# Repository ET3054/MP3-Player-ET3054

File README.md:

# MP3-Player-ET3054

Einrichtung:          		Hochschule für Wirtschaft und Recht Berlin

Jahrgang:                  	2024

Studierende:               	Bruno Storp
                           	Niclas Konzack
                           
Modul:                     	ET3054 Produktentwicklung

Zielsetzung des Projekts:  	Entwicklung eines MP3-Players, welcher auch leistungsstärkere Kopfhöher (Benchmark Sennheiser HD650) ohne qualitative Einschränkungen betreiben kann

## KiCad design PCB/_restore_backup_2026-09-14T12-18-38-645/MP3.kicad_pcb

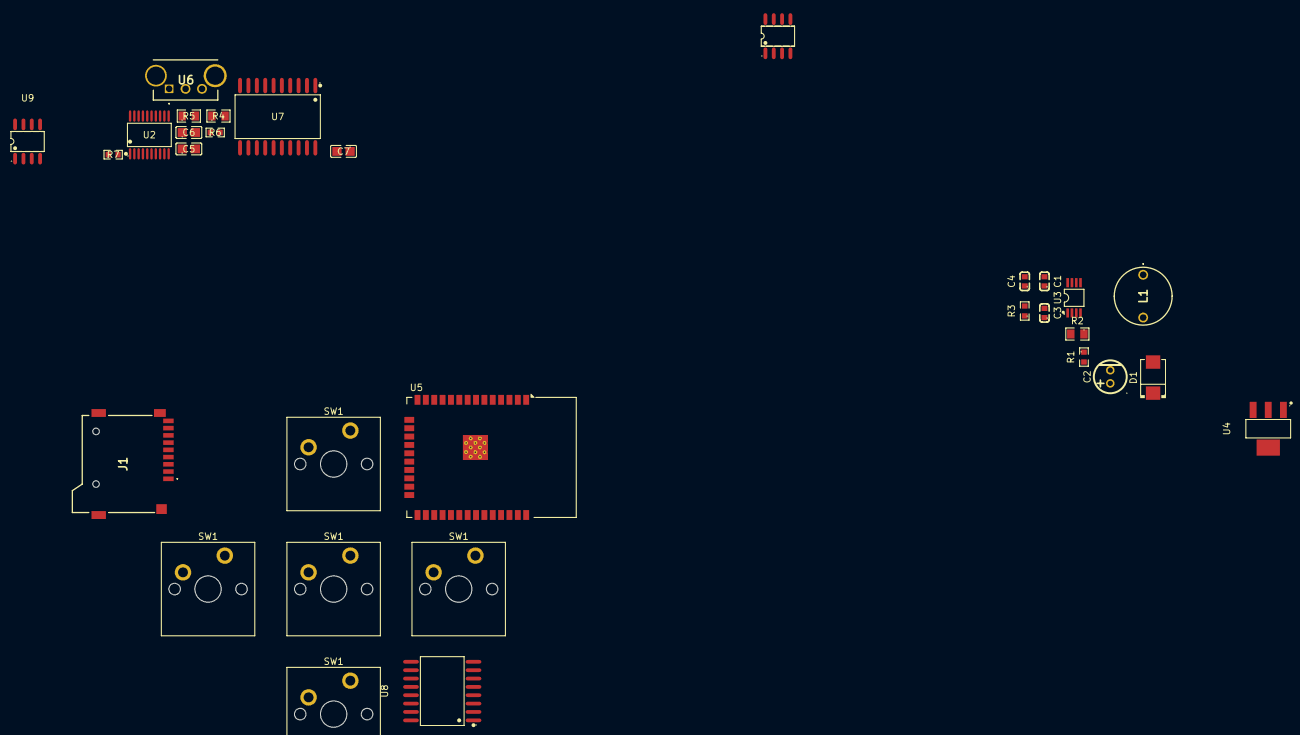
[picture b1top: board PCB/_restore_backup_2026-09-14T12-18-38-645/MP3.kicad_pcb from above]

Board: 2 copper layers, 31 parts (0 on the bottom side), 14 nets, no tracks yet.

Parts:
C1, C4: 33nF (333) ±10% 50V; C1614_C0603
C2: 47uF 35V; C40063_CAP-TH_BD5_0-P2_00-D0_8-FD
C3: 10pF (100) ±5% 50V; C1634_C0603
C5, C7: CL21A226MAYNNNE; C602037_C0805
C6: 47uF (476) ±20% 6.3V; C16780_C0805
D1: MBRS130LT3G; C51771_SMB_L4_6-W3_6-LS5_3-RD
J1: MSD-4-A; MSD4A
L1: 744750230150
R1: 147KΩ (1473) ±1%; C22878_R0603
R2, R4, R5: 10KΩ (1002) ±1%; C17414_R0805
R3: 20KΩ (2002) ±1%; C4184_R0603
R6, R7: 100KΩ (1003) ±1%; C25803_R0603
SW1, SW1#2, SW1#3, SW1#4, SW1#5: SW_Push; SW_Cherry_MX_PCB_1.00u
U1: AD8397ARZ-REEL7; C521305_SOIC-8_L4_9-W3_9-P1_27-LS6_0-BL
U2: PCM5102APWR; C107671_TSSOP-20_L6_5-W4_4-P0_65-LS6_4-BL
U3: ADP1613ARMZ-R7; C132279_MSOP-8_L3_0-W3_0-P0_65-LS4_9-BL
U4: LT3080EST#TRPBF; C107704_SOT-223_L6_5-W3_5-P2_30-LS7_0-BR_ST_VNL5050N3TR-E
U5: ESP32-WROOM-32D
U6: EC10E1260502
U7: LM1972MX/NOPB; C2649339_SOIC-20_L13_0-W7_6-P1_27-LS10_3-BL
U8: MC14490DWR2G; C223556_SOIC-16_L10_3-W7_5-P1_27-LS10_3-BL
U9: TLE2426ID; C353015_SOIC-8_L4_9-W3_9-P1_27-LS6_0-BL

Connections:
0: C1.2, C2.2, C3.2, C4.2, C6.1, R2.1, R5.1, U3.4 (GND)
+3.3V: L1.1, U3.3 (EN), U3.6 (VIN), U3.7 (FREQ)
+9V: R4.2, U7.3 (GND1), U7.19 (GND2)
unnamed: C4.1, R3.2
unnamed: C6.2, R4.1, R5.2, R6.1, R7.1 (1_1)
unnamed: D1.2 (A), L1.2, U3.5 (SW)
unnamed: C2.1, D1.1 (C), R1.2
unnamed: C5.1, U2.6 (OUTL_6)
unnamed: C3.1, R3.1, U3.1 (COMP)
unnamed: R1.1, R2.2, U3.2 (FB)
unnamed: C1.1, U3.8 (SS)
unnamed: U5.1 (GND), U5.15 (GND), U5.38 (GND), U5.39 (GND)
unnamed: C5.2, R6.2, U7.20 (IN2)
unnamed: C7.1 (1_1), U7.17 (OUT2)

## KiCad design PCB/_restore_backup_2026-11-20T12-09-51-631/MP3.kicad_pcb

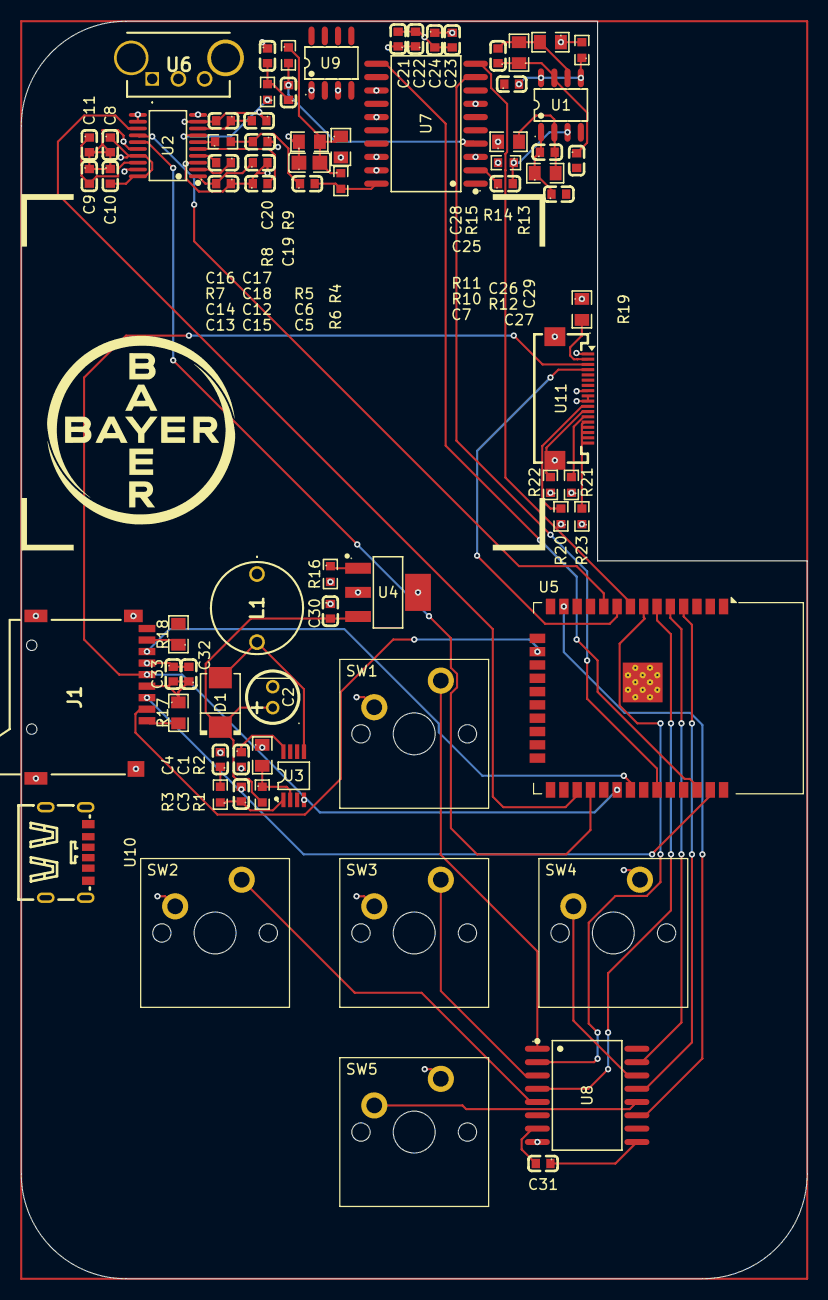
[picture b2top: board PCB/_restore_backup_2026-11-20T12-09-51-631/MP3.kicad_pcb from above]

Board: 4 copper layers, 75.0 x 120.0 mm, 75 parts (0 on the bottom side), 64 nets.

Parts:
C1, C4: 33nF (333) ±10% 50V; C1614_C0603
C2: 47uF 35V; C40063_CAP-TH_BD5_0-P2_00-D0_8-FD
C3: 10pF (100) ±5% 50V; C1634_C0603
C5, C19: 4.7uF (475) ±10% 10V; C1705_C0603
C6: 47uF (476) ±20% 6.3V; C16780_C0805
C7, C14, C15, C25, C27, C29: 2.2uF (225) ±10% 16V; C23630_C0603
C8, C9, C12, C16, C18, C20, C21, C24, C32: 100nF (104) ±10% 25V; C1590_C0603
C10, C11, C13, C17, C22, C23, C33: 贴片电容/10uF (106) ±20% 25V; C76614_C0603
C26, C28: 120pF; C107035_C0603
C30, C31: 1uF (105) ±10% 25V X7R; C29936_C0603
D1: MBRS130LT3G; C51771_SMB_L4_6-W3_6-LS5_3-RD
J1: MSD-4-A; MSD4A
L1: 744750230150
R1: 147KΩ (1473) ±1%; C22878_R0603
R2, R4, R5, R11, R12, R14, R15, R17, R18, R19: 10KΩ (1002) ±1%; C17414_R0805
R3: 20KΩ (2002) ±1%; C4184_R0603
R6, R9, R10, R13: 100KΩ (1003) ±1%; C25803_R0603
R7, R8: 470Ω (471) ±5%; C25241_R0603
R16: RC0603FR-071M8L; C137772_R0603
R20, R21, R22, R23: 27Ω (27R0) ±1%; C25190_R0603
SW1, SW2, SW3, SW4, SW5: SW_Push; SW_Cherry_MX_PCB_1.00u
U1: AD8397ARZ-REEL7; C521305_SOIC-8_L4_9-W3_9-P1_27-LS6_0-BL
U2: PCM5102APWR; C107671_TSSOP-20_L6_5-W4_4-P0_65-LS6_4-BL
U3: ADP1613ARMZ-R7; C132279_MSOP-8_L3_0-W3_0-P0_65-LS4_9-BL
U4: LT3080EST#TRPBF; C107704_SOT-223_L6_5-W3_5-P2_30-LS7_0-BR_ST_VNL5050N3TR-E
U5: ESP32-WROOM-32D
U6: EC10E1260502
U7: LM1972MX/NOPB; C2649339_SOIC-20_L13_0-W7_6-P1_27-LS10_3-BL
U8: MC14490DWR2G; C223556_SOIC-16_L10_3-W7_5-P1_27-LS10_3-BL
U9: TLE2426ID; C353015_SOIC-8_L4_9-W3_9-P1_27-LS6_0-BL
U10: USB-TYPE-C-009; C2927029_TYPE-C-SMD_TYPE-C-6P
U11: FPC 0.5-18P HYH2.0; C6364663_FPC-SMD_18P-P0_50_FPC-0_5-18P-HYH2_0

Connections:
0: C1.2, C2.2, C3.2, C4.2, C8.2, C9.1, C10.1, C11.2, C30.1, C32.1, C33.2, J1.6 (VSS), J1.G1 (GND_1), J1.G2 (GND_2), J1.G3 (GND_3), J1.G4 (GND_4), R2.1, R16.2, R20.1, R21.1, R22.1, R23.1, SW1.1, SW2.1, SW3.1, SW4.2, SW5.2, U1.4 (-VS), U2.10 (DEMP), U2.11 (FLT), U2.12 (SCK), U2.16 (FMT), U2.19 (DGND), U3.4 (GND), U7.1 (GND_AC), U7.5 (GND_AC), U7.6 (GND_AC), U7.8 (LOGIC_GND), U7.14 (GND_AC), U7.16 (GND_AC), U8.8 (VSS), U9.2 (COMMON), U11.1, U11.8, U11.19, U11.20
+3.3V: C8.1, C10.2, C32.2, C33.1, J1.4 (VDD), L1.1, R17.1, R18.2, R19.1, U2.17 (XSMT), U2.20 (DVDD), U3.3 (EN), U3.6 (VIN), U3.7 (FREQ), U8.16 (VDD), U11.9, U11.10
+9V: C21.2, C22.2, C23.2, C24.2, R4.2, R10.2, R11.1, R13.2, R14.1, U7.3 (GND1), U7.19 (GND2), U9.1 (OUT)
unnamed: C4.1, R3.2
unnamed: C6.2, R4.1, R5.2, R6.1, R9.1
unnamed: C5.1, C18.2, R7.2
unnamed: C19.1, C20.2, R8.2
unnamed: D1.2 (A), L1.2, U3.5 (SW)
unnamed: C2.1, C30.2, D1.1 (C), R1.2, U4.3 (IN*)
unnamed: J1.2 (CD/DAT3), U5.16 (IO13)
unnamed: J1.5 (CLK), U5.30 (IO18), U11.3
unnamed: J1.3 (CMD), U5.37 (IO23), U11.6
unnamed: J1.7 (DAT0), U5.31 (IO19)
unnamed: J1.8 (DAT1), R18.1
unnamed: J1.1 (DAT2), R17.2
unnamed: R20.2, U11.11
unnamed: R21.2, U11.12
unnamed: R22.2, U11.13
unnamed: R23.2, U11.14
unnamed: C7.2, R10.1, U1.3 (IN1+)
unnamed: C26.2, R11.2, R12.2, U1.2 (IN1-)
unnamed: C26.1, C27.1 (1_1), R12.1, U1.1 (OUT1)
unnamed: C25.2, R13.1, U1.5 (IN2+)
unnamed: C28.2, R14.2, R15.2, U1.6 (IN2-)
unnamed: C28.1, C29.1 (1_1), R15.1, U1.7 (OUT2)
unnamed: C6.1, C12.2, C13.1, C15.1, C16.2, C17.1, C18.1, C20.1, C23.1, C24.1, R5.1, U2.3 (CPGND), U2.9 (AGND), U7.7 (VSS2), U7.18 (VSS1)
unnamed: C12.1, C13.2, C16.1, C17.2, U2.1 (CPVDD), U2.8 (AVDD)
unnamed: U2.13 (BCK), U5.27 (IO16)
unnamed: C14.2, U2.4 (CAPM)
unnamed: C14.1, U2.2 (CAPP)
unnamed: U2.14 (DIN), U5.10 (IO25)
unnamed: C9.2, C11.1, U2.18 (LDOO)
unnamed: U2.15 (LRCK), U5.28 (IO17)
unnamed: R7.1, U2.6 (OUTL)
unnamed: R8.1, U2.7 (OUTR)
unnamed: C15.2, U2.5 (VNEG)
unnamed: C3.1, R3.1, U3.1 (COMP)
unnamed: R1.1, R2.2, U3.2 (FB)
unnamed: C1.1, U3.8 (SS)
unnamed: R16.1, U4.1 (SET)
unnamed: U5.1 (GND), U5.15 (GND), U5.38 (GND), U5.39 (GND)
unnamed: R19.2, U5.26 (IO4), U11.2
unnamed: U5.29 (IO5), U11.5
unnamed: U5.13 (IO14), U8.11 (Eout)
unnamed: U5.33 (IO21), U7.9 (CLOCK)
unnamed: U5.36 (IO22), U7.11 (DATA_IN)
unnamed: U5.8 (IO32), U7.10 (LOAD/SHIFT)
unnamed: U5.9 (IO33), U11.4
unnamed: U5.6 (IO34), U8.4 (Dout)
unnamed: U5.7 (IO35), U8.2 (Bout)
unnamed: U5.5 (SENSOR_VN), U8.15 (Aout)
unnamed: U5.4 (SENSOR_VP), U8.13 (Cout)
unnamed: C19.2, R9.2, U7.4 (IN1)
unnamed: C5.2, R6.2, U7.20 (IN2)
unnamed: C7.1, U7.2 (OUT1)
unnamed: C25.1, U7.17 (OUT2)
unnamed: SW1.2, U8.1 (Ain)
unnamed: SW4.1, U8.14 (Bin)
unnamed: SW3.2, U8.3 (Cin)
unnamed: SW5.1, U8.12 (Din)
unnamed: SW2.2, U8.5 (Ein)
unnamed: C31.2, U8.7 (OSCin)
unnamed: C31.1, U8.9 (OSCout)
VDD: C21.1, C22.1, U1.8 (+VS), U4.2 (OUT), U4.4 (OUT), U7.13 (VDD1), U7.15 (VDD2), U9.3 (IN)
